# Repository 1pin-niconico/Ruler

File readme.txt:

これは頒布した定規基板の設計データになります。
以下注意事項になります。
・本設計ファイルはKicad8.0.4以降でご使用いただけます。
・無料でご使用いただけますが、著作権を放棄したわけではありません。
・本リポジトリ以外での再配布は禁止です。
・自作発言等はしないでください。

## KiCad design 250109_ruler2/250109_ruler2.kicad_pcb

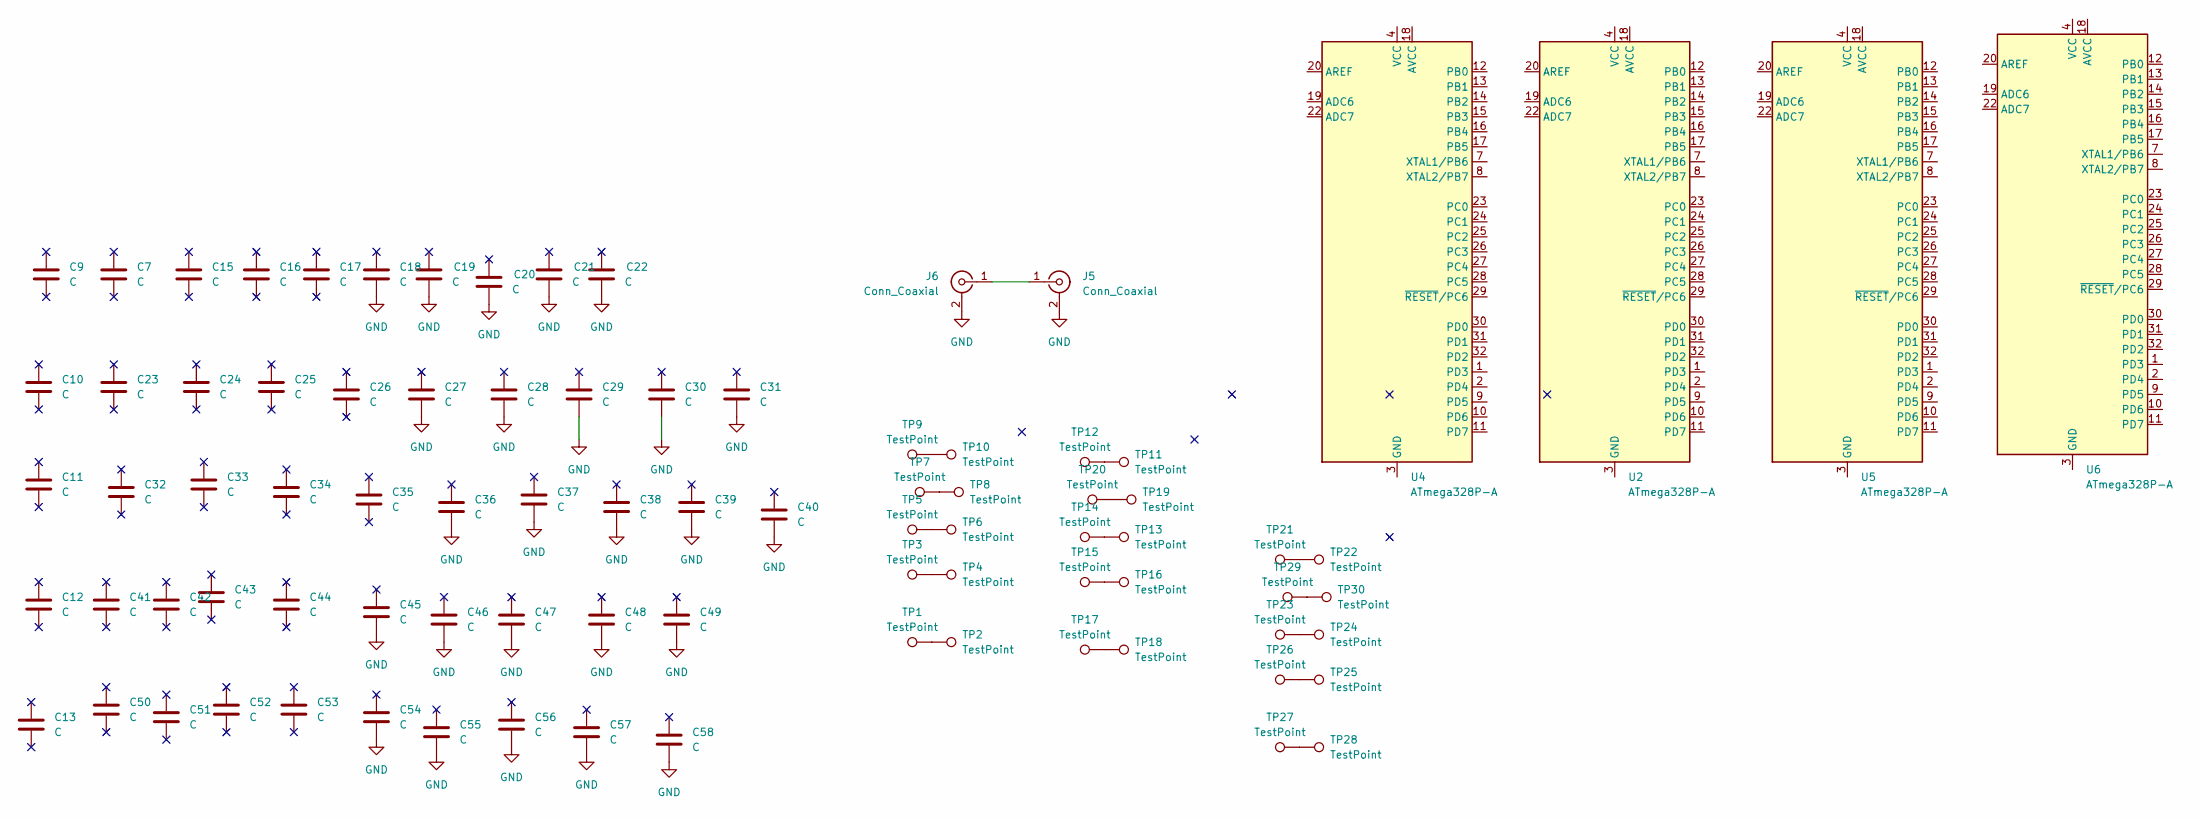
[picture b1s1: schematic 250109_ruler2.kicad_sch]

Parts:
C7, C9, C15, C16, C17, C18, C19, C20, C21, C22: C; C_0201_0603Metric_Pad0.64x0.40mm_HandSolder
C10, C23, C24, C25, C26, C27, C28, C29, C30, C31: C; C_0402_1005Metric_Pad0.74x0.62mm_HandSolder
C11, C32, C33, C34, C35, C36, C37, C38, C39, C40: C; C_0603_1608Metric_Pad1.08x0.95mm_HandSolder
C12, C41, C42, C43, C44, C45, C46, C47, C48, C49: C; C_0805_2012Metric_Pad1.18x1.45mm_HandSolder
C13, C50, C51, C52, C53, C54, C55, C56, C57, C58: C; C_1206_3216Metric_Pad1.33x1.80mm_HandSolder
J5, J6: Conn_Coaxial; SMA_Samtec_SMA-J-P-H-ST-EM1_EdgeMount
TP1, TP2, TP3, TP4, TP5, TP6, TP7, TP8, TP9, TP10, TP11, TP12, TP13, TP14, TP15, TP16, TP17, TP18, TP19, TP20, TP21, TP22, TP23, TP24, TP25, TP26, TP27, TP28, TP29, TP30: TestPoint; TestPoint_Pad_D3.0mm
U2, U4, U5, U6: ATmega328P-A; TQFP-32_7x7mm_P0.8mm

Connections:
GND: C18.2, C19.2, C20.2, C21.2, C22.2, C27.2, C28.2, C29.2, C30.2, C31.2, C36.2, C37.2, C38.2, C39.2, C40.2, C45.2, C46.2, C47.2, C48.2, C49.2, C54.2, C55.2, C56.2, C57.2, C58.2, J5.2 (Ext), J6.2 (Ext)
unnamed: J5.1 (In), J6.1 (In)
unnamed: TP1.1, TP2.1
unnamed: TP3.1, TP4.1
unnamed: TP5.1, TP6.1
unnamed: TP7.1, TP8.1
unnamed: TP9.1, TP10.1
unnamed: TP11.1, TP12.1
unnamed: TP13.1, TP14.1
unnamed: TP15.1, TP16.1
unnamed: TP17.1, TP18.1
unnamed: TP19.1, TP20.1
unnamed: TP21.1, TP22.1
unnamed: TP23.1, TP24.1
unnamed: TP25.1, TP26.1
unnamed: TP27.1, TP28.1
unnamed: TP29.1, TP30.1
unnamed: U2.4 (VCC), U2.6 (VCC)
unnamed: U2.3 (GND), U2.5 (GND), U2.21 (GND)
unnamed: U4.3 (GND), U4.5 (GND), U4.21 (GND)
unnamed: U4.4 (VCC), U4.6 (VCC)
unnamed: U5.4 (VCC), U5.6 (VCC)
unnamed: U5.3 (GND), U5.5 (GND), U5.21 (GND)
unnamed: U6.4 (VCC), U6.6 (VCC)
unnamed: U6.3 (GND), U6.5 (GND), U6.21 (GND)

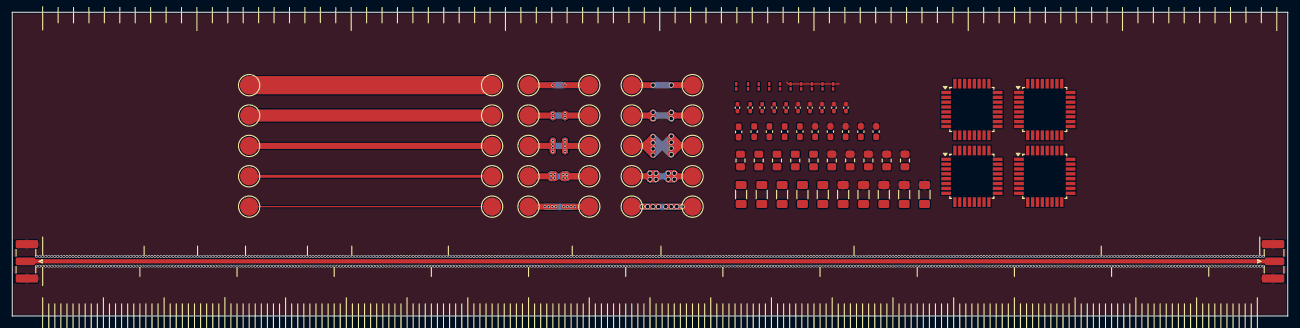
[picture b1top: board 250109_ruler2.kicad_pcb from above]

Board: 2 copper layers, 210.0 x 50.0 mm, 86 parts (0 on the bottom side), 19 nets.

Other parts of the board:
U4#2, U4#3, U4#4: ATmega328P-A; TQFP-32_7x7mm_P0.8mm
